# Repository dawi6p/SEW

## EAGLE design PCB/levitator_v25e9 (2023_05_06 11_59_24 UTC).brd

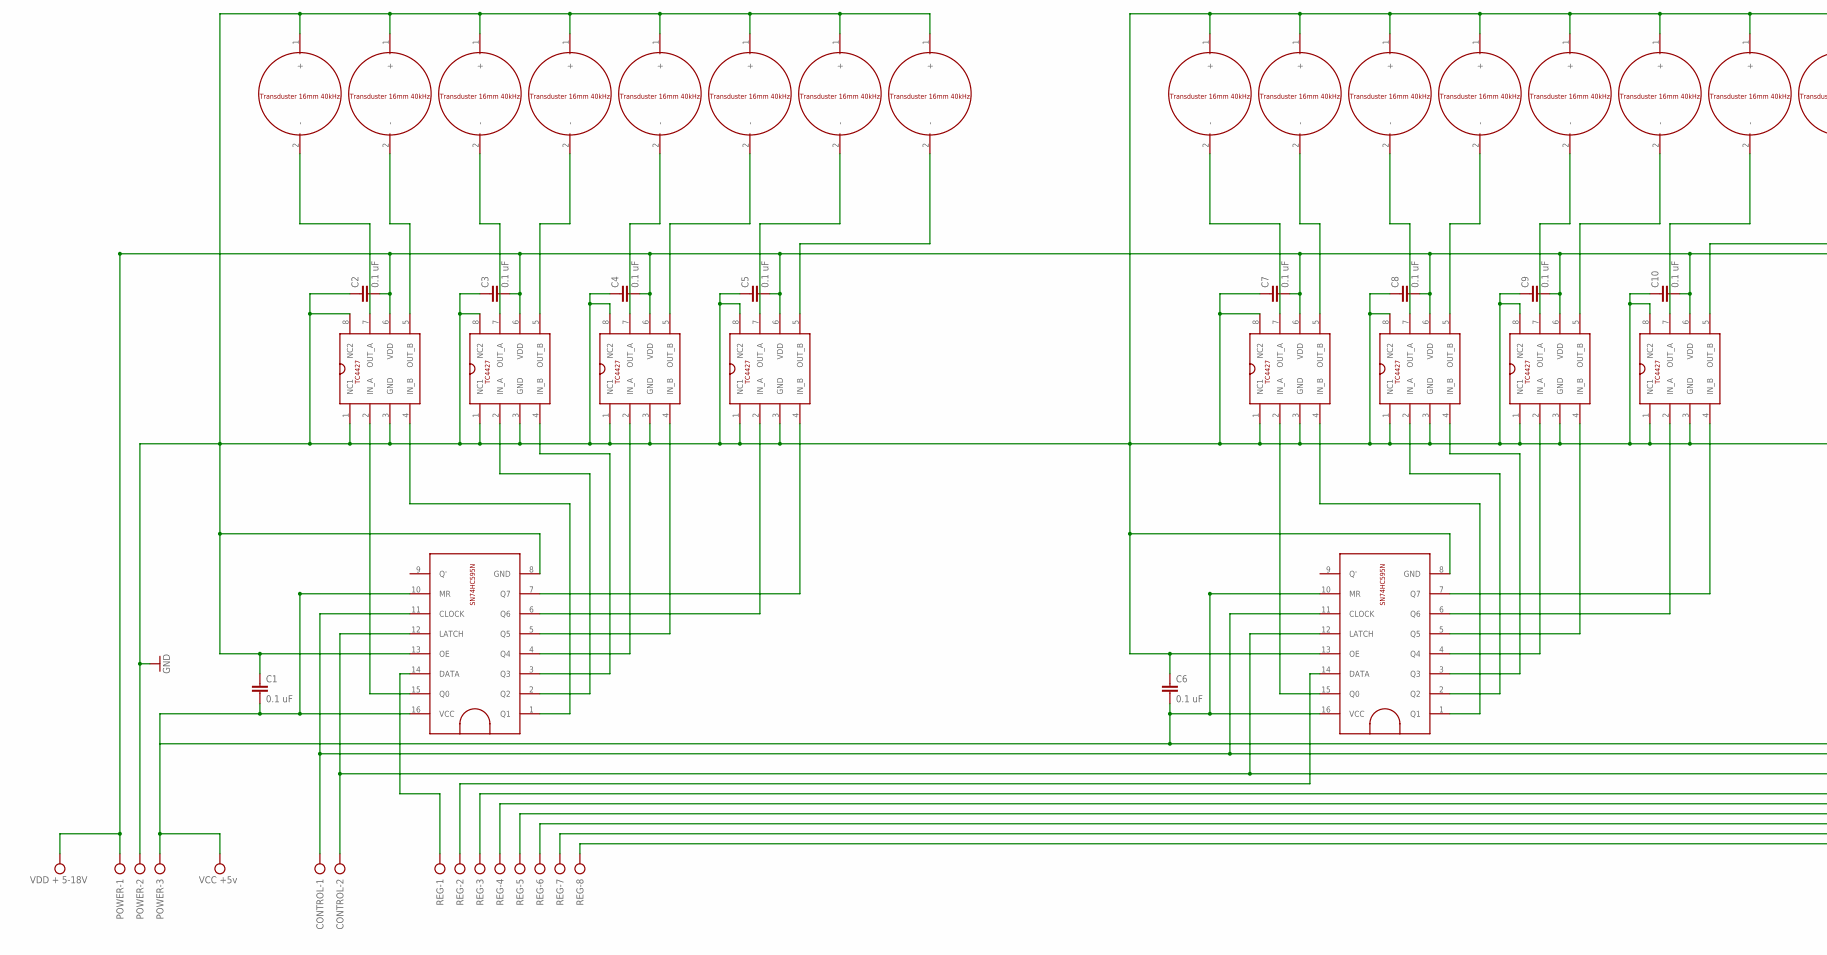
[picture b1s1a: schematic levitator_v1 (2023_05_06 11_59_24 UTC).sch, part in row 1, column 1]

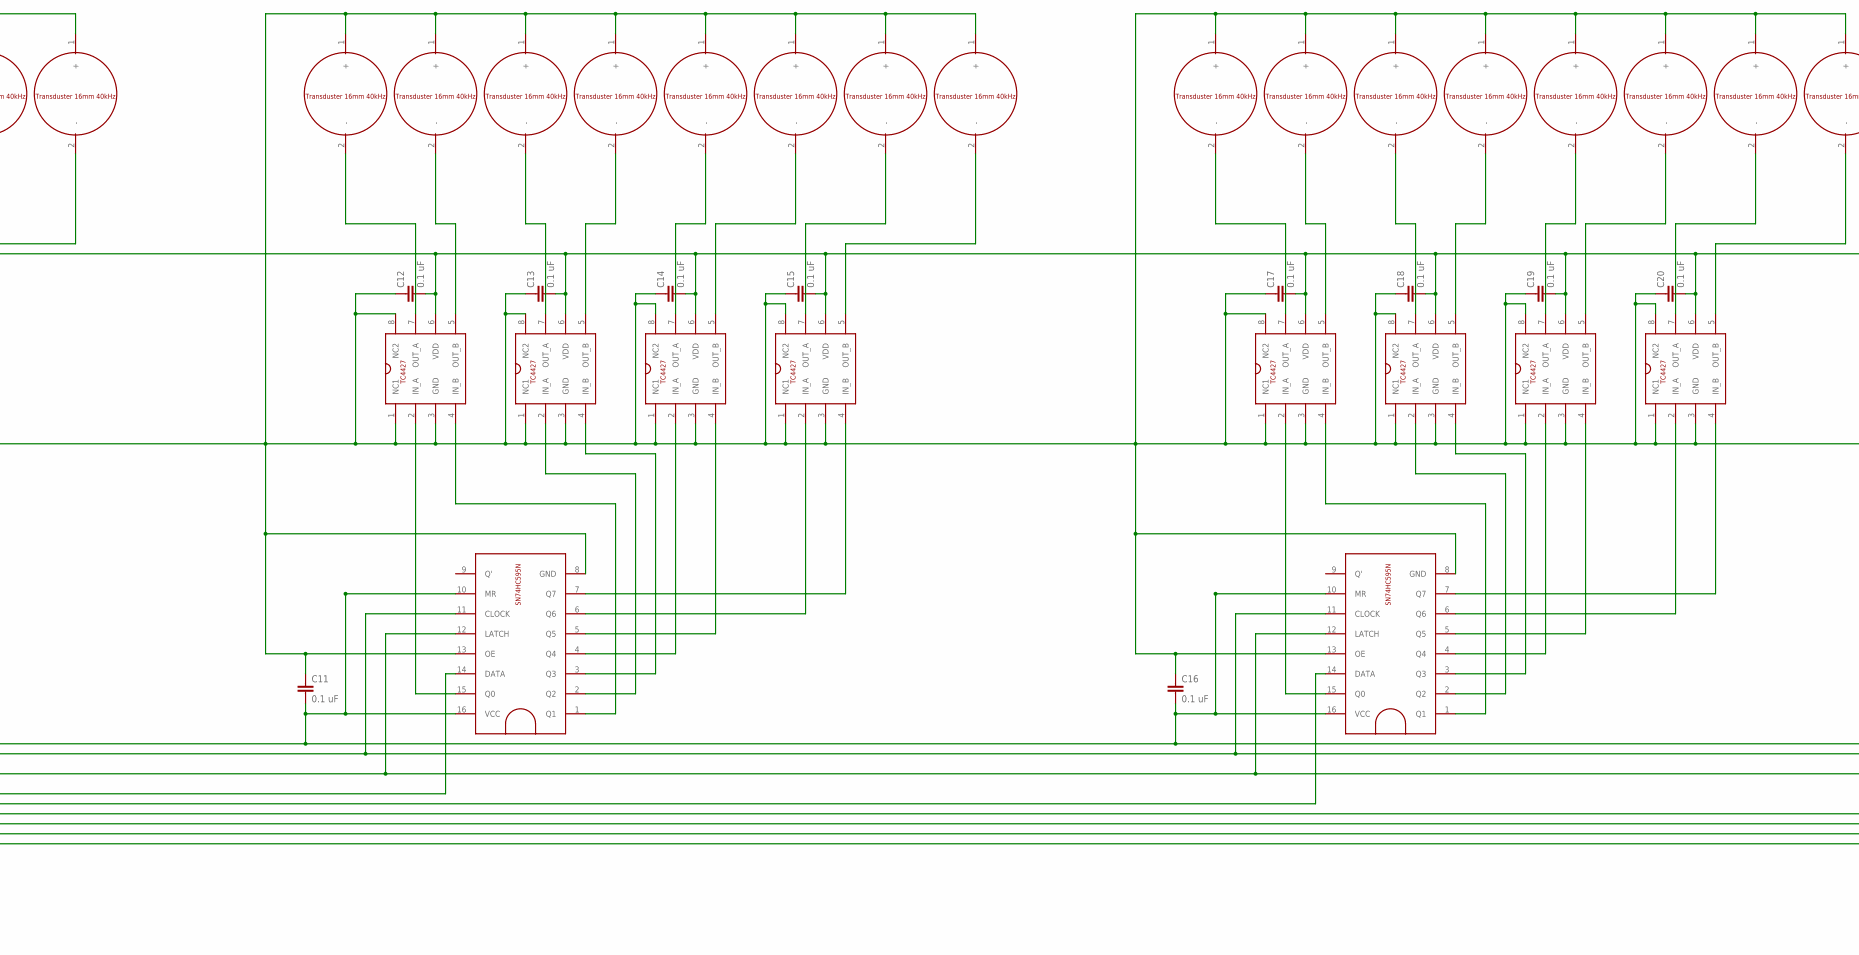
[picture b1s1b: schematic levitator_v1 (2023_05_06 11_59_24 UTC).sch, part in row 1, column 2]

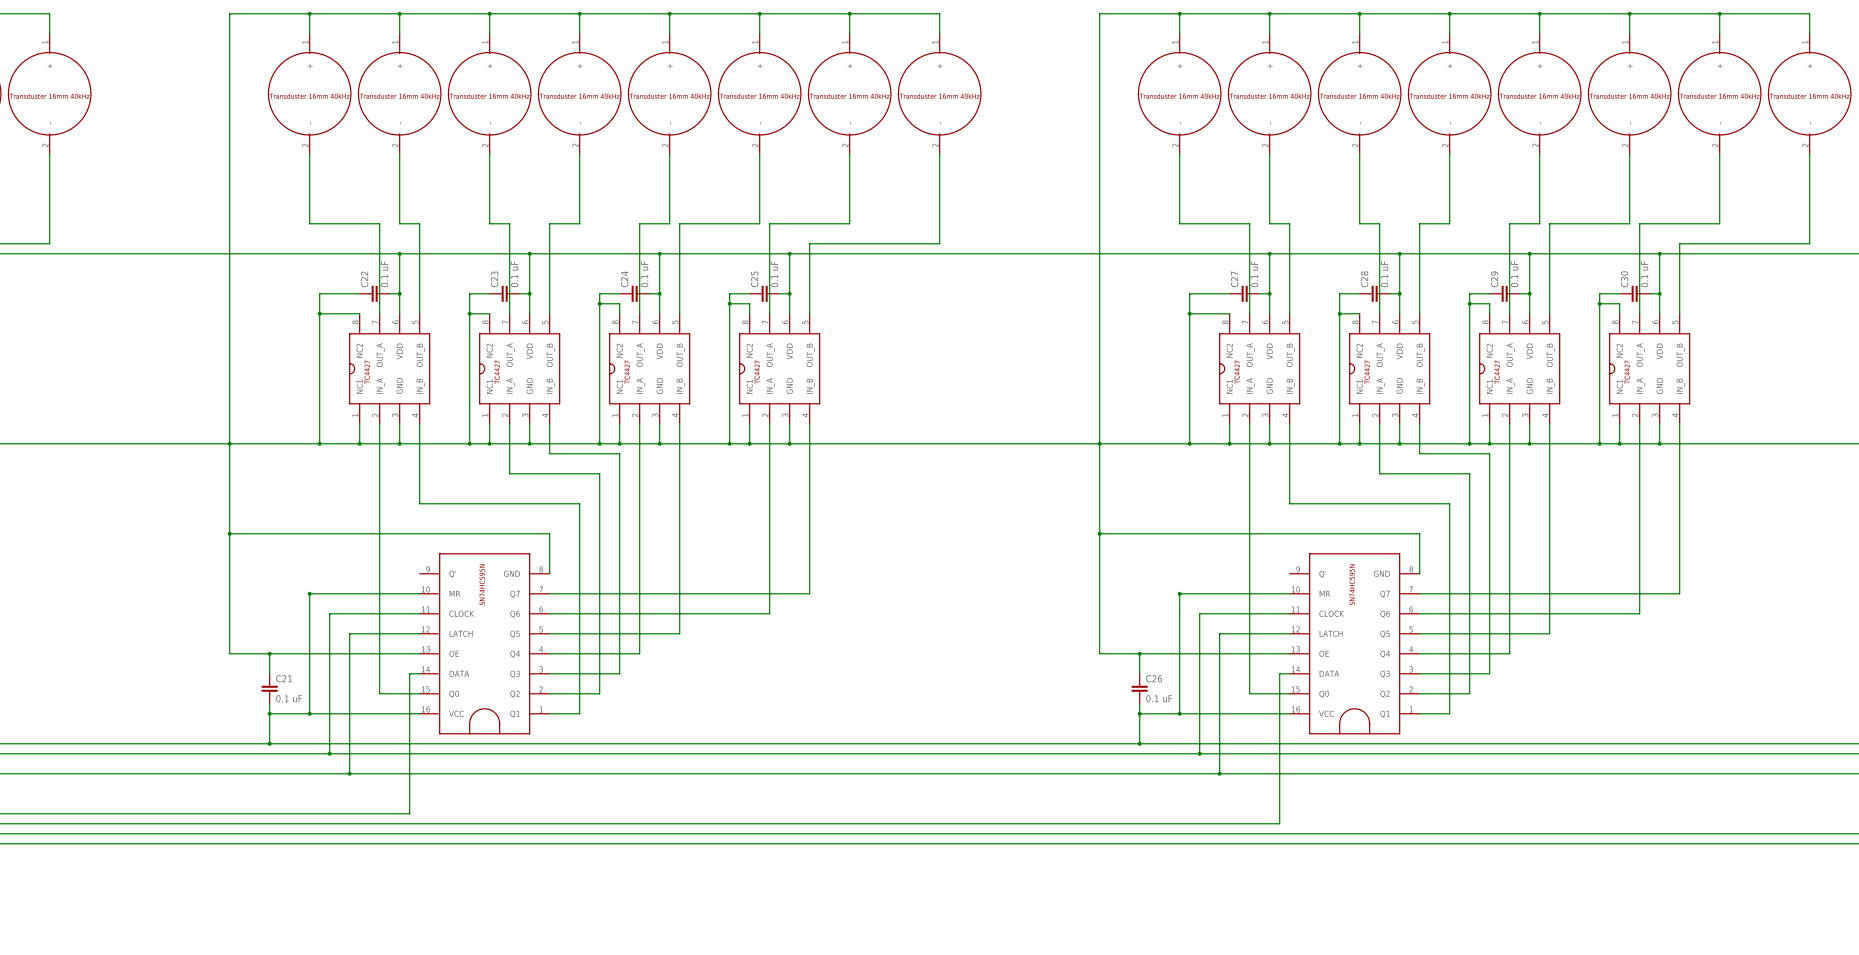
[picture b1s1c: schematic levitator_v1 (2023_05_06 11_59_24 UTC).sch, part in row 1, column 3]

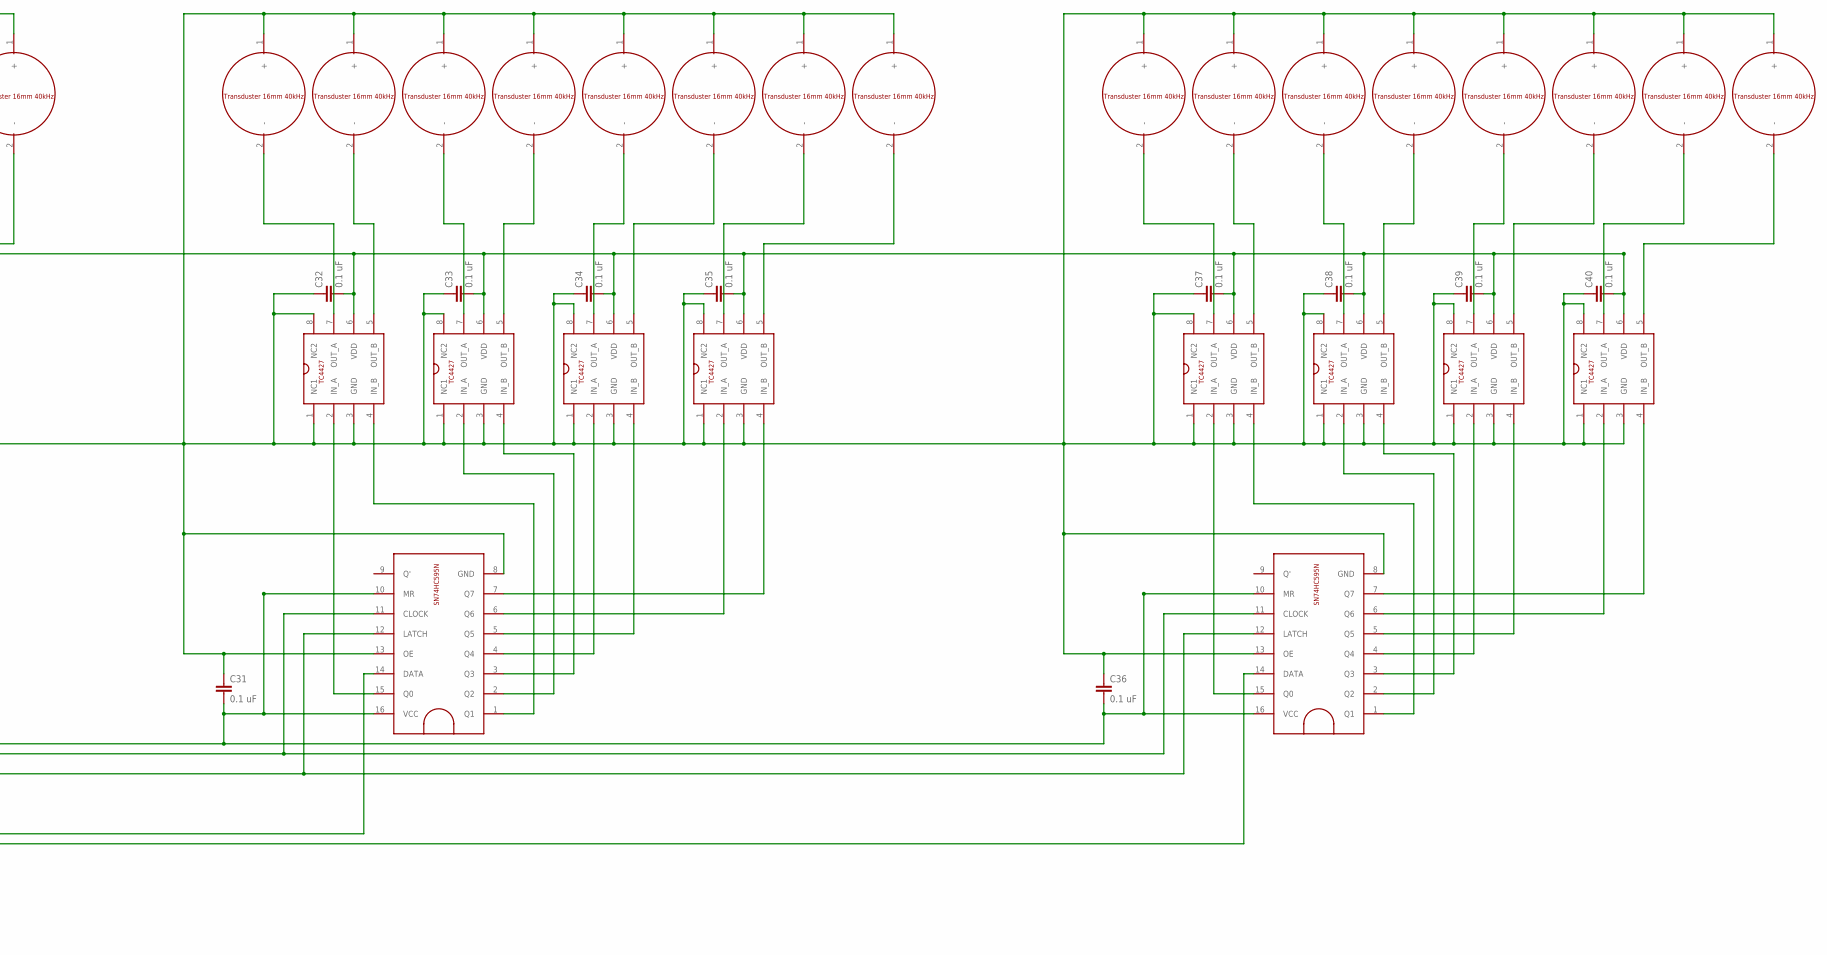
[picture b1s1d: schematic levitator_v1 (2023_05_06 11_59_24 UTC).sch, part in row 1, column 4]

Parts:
C1, C2, C3, C4, C5, C6, C7, C8, C9, C10, C11, C12, C13, C14, C15, C16, C17, C18, C19, C20, C21, C22, C23, C24, C25, C26, C27, C28, C29, C30, C31, C32, C33, C34, C35, C36, C37, C38, C39, C40: 0.1 uF; C025-025X050
CONTROL: AK500/2-H
POWER: AK500/3-H
REG: AK500/8-H
U$1, U$3, U$4, U$5, U$14, U$16, U$17, U$18, U$27, U$29, U$30, U$31, U$40, U$42, U$43, U$44, U$53, U$55, U$56, U$57, U$66, U$68, U$69, U$70, U$79, U$81, U$82, U$83, U$92, U$94, U$95, U$96: TC4427
U$2, U$15, U$28, U$41, U$54, U$67, U$80, U$93: SN74HC595N
U$6, U$7, U$8, U$9, U$10, U$11, U$12, U$13, U$19, U$20, U$21, U$22, U$23, U$24, U$25, U$26, U$32, U$33, U$34, U$35, U$36, U$37, U$38, U$39, U$45, U$46, U$47, U$48, U$49, U$50, U$51, U$52, U$58, U$59, U$60, U$61, U$62, U$63, U$64, U$65, U$71, U$72, U$73, U$74, U$75, U$76, U$77, U$78, U$84, U$85, U$86, U$87, U$88, U$89, U$90, U$91, U$97, U$98, U$99, U$100, U$101, U$102, U$103, U$104: TRANSDUSTER_16MM_40KHZ

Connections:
GND: C1.1, C2.1, C3.1, C4.1, C5.1, C6.1, C7.1, C8.1, C9.1, C10.1, C11.1, C12.1, C13.1, C14.1, C15.1, C16.1, C17.1, C18.1, C19.1, C20.1, C21.1, C22.1, C23.1, C24.1, C25.1, C26.1, C27.1, C28.1, C29.1, C30.1, C31.1, C32.1, C33.1, C34.1, C35.1, C36.1, C37.1, C38.1, C39.1, C40.1, POWER.2, U$1.1 (NC1), U$1.3 (GND), U$1.8 (NC2), U$2.8 (GND), U$2.13 (OE), U$3.1 (NC1), U$3.3 (GND), U$3.8 (NC2), U$4.1 (NC1), U$4.3 (GND), U$4.8 (NC2), U$5.1 (NC1), U$5.3 (GND), U$5.8 (NC2), U$6.1 (+), U$7.1 (+), U$8.1 (+), U$9.1 (+), U$10.1 (+), U$11.1 (+), U$12.1 (+), U$13.1 (+), U$14.1 (NC1), U$14.3 (GND), U$14.8 (NC2), U$15.8 (GND), U$15.13 (OE), U$16.1 (NC1), U$16.3 (GND), U$16.8 (NC2), U$17.1 (NC1), U$17.3 (GND), U$17.8 (NC2), U$18.1 (NC1), U$18.3 (GND), U$18.8 (NC2), U$19.1 (+), U$20.1 (+), U$21.1 (+), U$22.1 (+), U$23.1 (+), U$24.1 (+), U$25.1 (+), U$26.1 (+), U$27.1 (NC1), U$27.3 (GND), U$27.8 (NC2), U$28.8 (GND), U$28.13 (OE), U$29.1 (NC1), U$29.3 (GND), U$29.8 (NC2), U$30.1 (NC1), U$30.3 (GND), U$30.8 (NC2), U$31.1 (NC1), U$31.3 (GND), U$31.8 (NC2), U$32.1 (+), U$33.1 (+), U$34.1 (+), U$35.1 (+), U$36.1 (+), U$37.1 (+), U$38.1 (+), U$39.1 (+), U$40.1 (NC1), U$40.3 (GND), U$40.8 (NC2), U$41.8 (GND), U$41.13 (OE), U$42.1 (NC1), U$42.3 (GND), U$42.8 (NC2), U$43.1 (NC1), U$43.3 (GND), U$43.8 (NC2), U$44.1 (NC1), U$44.3 (GND), U$44.8 (NC2), U$45.1 (+), U$46.1 (+), U$47.1 (+), U$48.1 (+), U$49.1 (+), U$50.1 (+), U$51.1 (+), U$52.1 (+), U$53.1 (NC1), U$53.3 (GND), U$53.8 (NC2), U$54.8 (GND), U$54.13 (OE), U$55.1 (NC1), U$55.3 (GND), U$55.8 (NC2), U$56.1 (NC1), U$56.3 (GND), U$56.8 (NC2), U$57.1 (NC1), U$57.3 (GND), U$57.8 (NC2), U$58.1 (+), U$59.1 (+), U$60.1 (+), U$61.1 (+), U$62.1 (+), U$63.1 (+), U$64.1 (+), U$65.1 (+), U$66.1 (NC1), U$66.3 (GND), U$66.8 (NC2), U$67.8 (GND), U$67.13 (OE), U$68.1 (NC1), U$68.3 (GND), U$68.8 (NC2), U$69.1 (NC1), U$69.3 (GND), U$69.8 (NC2), U$70.1 (NC1), U$70.3 (GND), U$70.8 (NC2), U$71.1 (+), U$72.1 (+), U$73.1 (+), U$74.1 (+), U$75.1 (+), U$76.1 (+), U$77.1 (+), U$78.1 (+), U$79.1 (NC1), U$79.3 (GND), U$79.8 (NC2), U$80.8 (GND), U$80.13 (OE), U$81.1 (NC1), U$81.3 (GND), U$81.8 (NC2), U$82.1 (NC1), U$82.3 (GND), U$82.8 (NC2), U$83.1 (NC1), U$83.3 (GND), U$83.8 (NC2), U$84.1 (+), U$85.1 (+), U$86.1 (+), U$87.1 (+), U$88.1 (+), U$89.1 (+), U$90.1 (+), U$91.1 (+), U$92.1 (NC1), U$92.3 (GND), U$92.8 (NC2), U$93.8 (GND), U$93.13 (OE), U$94.1 (NC1), U$94.3 (GND), U$94.8 (NC2), U$95.1 (NC1), U$95.3 (GND), U$95.8 (NC2), U$96.1 (NC1), U$96.3 (GND), U$96.8 (NC2), U$97.1 (+), U$98.1 (+), U$99.1 (+), U$100.1 (+), U$101.1 (+), U$102.1 (+), U$103.1 (+), U$104.1 (+)
unnamed: U$1.2 (IN_A), U$2.15 (Q0)
unnamed: U$1.4 (IN_B), U$2.1 (Q1)
unnamed: U$2.2 (Q2), U$3.2 (IN_A)
unnamed: U$2.3 (Q3), U$3.4 (IN_B)
unnamed: U$2.4 (Q4), U$4.2 (IN_A)
unnamed: U$2.5 (Q5), U$4.4 (IN_B)
unnamed: U$2.6 (Q6), U$5.2 (IN_A)
unnamed: U$2.7 (Q7), U$5.4 (IN_B)
unnamed: U$1.7 (OUT_A), U$6.2 (-)
unnamed: U$1.5 (OUT_B), U$7.2 (-)
unnamed: U$3.7 (OUT_A), U$8.2 (-)
unnamed: U$3.5 (OUT_B), U$9.2 (-)
unnamed: U$4.7 (OUT_A), U$10.2 (-)
unnamed: U$4.5 (OUT_B), U$11.2 (-)
unnamed: U$5.7 (OUT_A), U$12.2 (-)
unnamed: U$5.5 (OUT_B), U$13.2 (-)
unnamed: REG.1, U$2.14 (DATA)
unnamed: U$79.2 (IN_A), U$80.15 (Q0)
unnamed: U$79.4 (IN_B), U$80.1 (Q1)
unnamed: U$14.2 (IN_A), U$15.15 (Q0)
unnamed: U$14.4 (IN_B), U$15.1 (Q1)
unnamed: U$15.2 (Q2), U$16.2 (IN_A)
unnamed: U$15.3 (Q3), U$16.4 (IN_B)
unnamed: U$15.4 (Q4), U$17.2 (IN_A)
unnamed: U$15.5 (Q5), U$17.4 (IN_B)
unnamed: U$15.6 (Q6), U$18.2 (IN_A)
unnamed: U$15.7 (Q7), U$18.4 (IN_B)
unnamed: U$14.7 (OUT_A), U$19.2 (-)
unnamed: U$14.5 (OUT_B), U$20.2 (-)
unnamed: U$16.7 (OUT_A), U$21.2 (-)
unnamed: U$16.5 (OUT_B), U$22.2 (-)
unnamed: U$17.7 (OUT_A), U$23.2 (-)
unnamed: U$17.5 (OUT_B), U$24.2 (-)
unnamed: U$18.7 (OUT_A), U$25.2 (-)
unnamed: U$18.5 (OUT_B), U$26.2 (-)
unnamed: REG.2, U$15.14 (DATA)
unnamed: U$27.2 (IN_A), U$28.15 (Q0)
unnamed: U$27.4 (IN_B), U$28.1 (Q1)
unnamed: U$28.2 (Q2), U$29.2 (IN_A)
unnamed: U$28.3 (Q3), U$29.4 (IN_B)
unnamed: U$28.4 (Q4), U$30.2 (IN_A)
unnamed: U$28.5 (Q5), U$30.4 (IN_B)
unnamed: U$28.6 (Q6), U$31.2 (IN_A)
unnamed: U$28.7 (Q7), U$31.4 (IN_B)
unnamed: U$27.7 (OUT_A), U$32.2 (-)
unnamed: U$27.5 (OUT_B), U$33.2 (-)
unnamed: U$29.7 (OUT_A), U$34.2 (-)
unnamed: U$29.5 (OUT_B), U$35.2 (-)
unnamed: U$30.7 (OUT_A), U$36.2 (-)
unnamed: U$30.5 (OUT_B), U$37.2 (-)
unnamed: U$31.7 (OUT_A), U$38.2 (-)
unnamed: U$31.5 (OUT_B), U$39.2 (-)
unnamed: REG.3, U$28.14 (DATA)
unnamed: U$80.2 (Q2), U$81.2 (IN_A)
unnamed: CONTROL.1, U$2.11 (CLOCK), U$15.11 (CLOCK), U$28.11 (CLOCK), U$41.11 (CLOCK), U$54.11 (CLOCK), U$67.11 (CLOCK), U$80.11 (CLOCK), U$93.11 (CLOCK)
unnamed: CONTROL.2, U$2.12 (LATCH), U$15.12 (LATCH), U$28.12 (LATCH), U$41.12 (LATCH), U$54.12 (LATCH), U$67.12 (LATCH), U$80.12 (LATCH), U$93.12 (LATCH)
unnamed: U$40.2 (IN_A), U$41.15 (Q0)
unnamed: U$40.4 (IN_B), U$41.1 (Q1)
unnamed: U$41.2 (Q2), U$42.2 (IN_A)
unnamed: U$41.3 (Q3), U$42.4 (IN_B)
unnamed: U$41.4 (Q4), U$43.2 (IN_A)
unnamed: U$41.5 (Q5), U$43.4 (IN_B)
unnamed: U$41.6 (Q6), U$44.2 (IN_A)
unnamed: U$41.7 (Q7), U$44.4 (IN_B)
unnamed: U$40.7 (OUT_A), U$45.2 (-)
unnamed: U$40.5 (OUT_B), U$46.2 (-)
unnamed: U$42.7 (OUT_A), U$47.2 (-)
unnamed: U$42.5 (OUT_B), U$48.2 (-)
unnamed: U$43.7 (OUT_A), U$49.2 (-)
unnamed: U$43.5 (OUT_B), U$50.2 (-)
unnamed: U$44.7 (OUT_A), U$51.2 (-)
unnamed: U$44.5 (OUT_B), U$52.2 (-)
unnamed: REG.4, U$41.14 (DATA)
unnamed: U$80.3 (Q3), U$81.4 (IN_B)
unnamed: U$53.2 (IN_A), U$54.15 (Q0)
unnamed: U$53.4 (IN_B), U$54.1 (Q1)
unnamed: U$54.2 (Q2), U$55.2 (IN_A)
unnamed: U$54.3 (Q3), U$55.4 (IN_B)
unnamed: U$54.4 (Q4), U$56.2 (IN_A)
unnamed: U$54.5 (Q5), U$56.4 (IN_B)
unnamed: U$54.6 (Q6), U$57.2 (IN_A)
unnamed: U$54.7 (Q7), U$57.4 (IN_B)
unnamed: U$53.7 (OUT_A), U$58.2 (-)
unnamed: U$53.5 (OUT_B), U$59.2 (-)
unnamed: U$55.7 (OUT_A), U$60.2 (-)
unnamed: U$55.5 (OUT_B), U$61.2 (-)
unnamed: U$56.7 (OUT_A), U$62.2 (-)
unnamed: U$56.5 (OUT_B), U$63.2 (-)
unnamed: U$57.7 (OUT_A), U$64.2 (-)
unnamed: U$57.5 (OUT_B), U$65.2 (-)
unnamed: REG.5, U$54.14 (DATA)
unnamed: U$66.2 (IN_A), U$67.15 (Q0)
unnamed: U$66.4 (IN_B), U$67.1 (Q1)
unnamed: U$67.2 (Q2), U$68.2 (IN_A)
unnamed: U$67.3 (Q3), U$68.4 (IN_B)
unnamed: U$67.4 (Q4), U$69.2 (IN_A)
unnamed: U$67.5 (Q5), U$69.4 (IN_B)
unnamed: U$67.6 (Q6), U$70.2 (IN_A)
unnamed: U$67.7 (Q7), U$70.4 (IN_B)
unnamed: U$66.7 (OUT_A), U$71.2 (-)
unnamed: U$66.5 (OUT_B), U$72.2 (-)
unnamed: U$68.7 (OUT_A), U$73.2 (-)
unnamed: U$68.5 (OUT_B), U$74.2 (-)
unnamed: U$69.7 (OUT_A), U$75.2 (-)
unnamed: U$69.5 (OUT_B), U$76.2 (-)
unnamed: U$70.7 (OUT_A), U$77.2 (-)
unnamed: U$70.5 (OUT_B), U$78.2 (-)
unnamed: REG.6, U$67.14 (DATA)
unnamed: U$80.4 (Q4), U$82.2 (IN_A)
unnamed: U$80.5 (Q5), U$82.4 (IN_B)
unnamed: U$80.6 (Q6), U$83.2 (IN_A)
unnamed: U$80.7 (Q7), U$83.4 (IN_B)
unnamed: U$79.7 (OUT_A), U$84.2 (-)
unnamed: U$79.5 (OUT_B), U$85.2 (-)
unnamed: U$81.7 (OUT_A), U$86.2 (-)
unnamed: U$81.5 (OUT_B), U$87.2 (-)
unnamed: U$82.7 (OUT_A), U$88.2 (-)
unnamed: U$82.5 (OUT_B), U$89.2 (-)
unnamed: U$83.7 (OUT_A), U$90.2 (-)
unnamed: U$83.5 (OUT_B), U$91.2 (-)
unnamed: REG.7, U$80.14 (DATA)
unnamed: U$92.2 (IN_A), U$93.15 (Q0)
unnamed: U$92.4 (IN_B), U$93.1 (Q1)
unnamed: U$93.2 (Q2), U$94.2 (IN_A)
unnamed: U$93.3 (Q3), U$94.4 (IN_B)
unnamed: U$93.4 (Q4), U$95.2 (IN_A)
unnamed: U$93.5 (Q5), U$95.4 (IN_B)
unnamed: U$93.6 (Q6), U$96.2 (IN_A)
unnamed: U$93.7 (Q7), U$96.4 (IN_B)
unnamed: U$92.7 (OUT_A), U$97.2 (-)
unnamed: U$92.5 (OUT_B), U$98.2 (-)
unnamed: U$94.7 (OUT_A), U$99.2 (-)
unnamed: U$94.5 (OUT_B), U$100.2 (-)
unnamed: U$95.7 (OUT_A), U$101.2 (-)
unnamed: U$95.5 (OUT_B), U$102.2 (-)
unnamed: U$96.7 (OUT_A), U$103.2 (-)
unnamed: U$96.5 (OUT_B), U$104.2 (-)
unnamed: REG.8, U$93.14 (DATA)
VCC: C1.2, C6.2, C11.2, C16.2, C21.2, C26.2, C31.2, C36.2, POWER.3, U$2.10 (MR), U$2.16 (VCC), U$15.10 (MR), U$15.16 (VCC), U$28.10 (MR), U$28.16 (VCC), U$41.10 (MR), U$41.16 (VCC), U$54.10 (MR), U$54.16 (VCC), U$67.10 (MR), U$67.16 (VCC), U$80.10 (MR), U$80.16 (VCC), U$93.10 (MR), U$93.16 (VCC)
VDD: C2.2, C3.2, C4.2, C5.2, C7.2, C8.2, C9.2, C10.2, C12.2, C13.2, C14.2, C15.2, C17.2, C18.2, C19.2, C20.2, C22.2, C23.2, C24.2, C25.2, C27.2, C28.2, C29.2, C30.2, C32.2, C33.2, C34.2, C35.2, C37.2, C38.2, C39.2, C40.2, POWER.1, U$1.6 (VDD), U$3.6 (VDD), U$4.6 (VDD), U$5.6 (VDD), U$14.6 (VDD), U$16.6 (VDD), U$17.6 (VDD), U$18.6 (VDD), U$27.6 (VDD), U$29.6 (VDD), U$30.6 (VDD), U$31.6 (VDD), U$40.6 (VDD), U$42.6 (VDD), U$43.6 (VDD), U$44.6 (VDD), U$53.6 (VDD), U$55.6 (VDD), U$56.6 (VDD), U$57.6 (VDD), U$66.6 (VDD), U$68.6 (VDD), U$69.6 (VDD), U$70.6 (VDD), U$79.6 (VDD), U$81.6 (VDD), U$82.6 (VDD), U$83.6 (VDD), U$92.6 (VDD), U$94.6 (VDD), U$95.6 (VDD), U$96.6 (VDD)

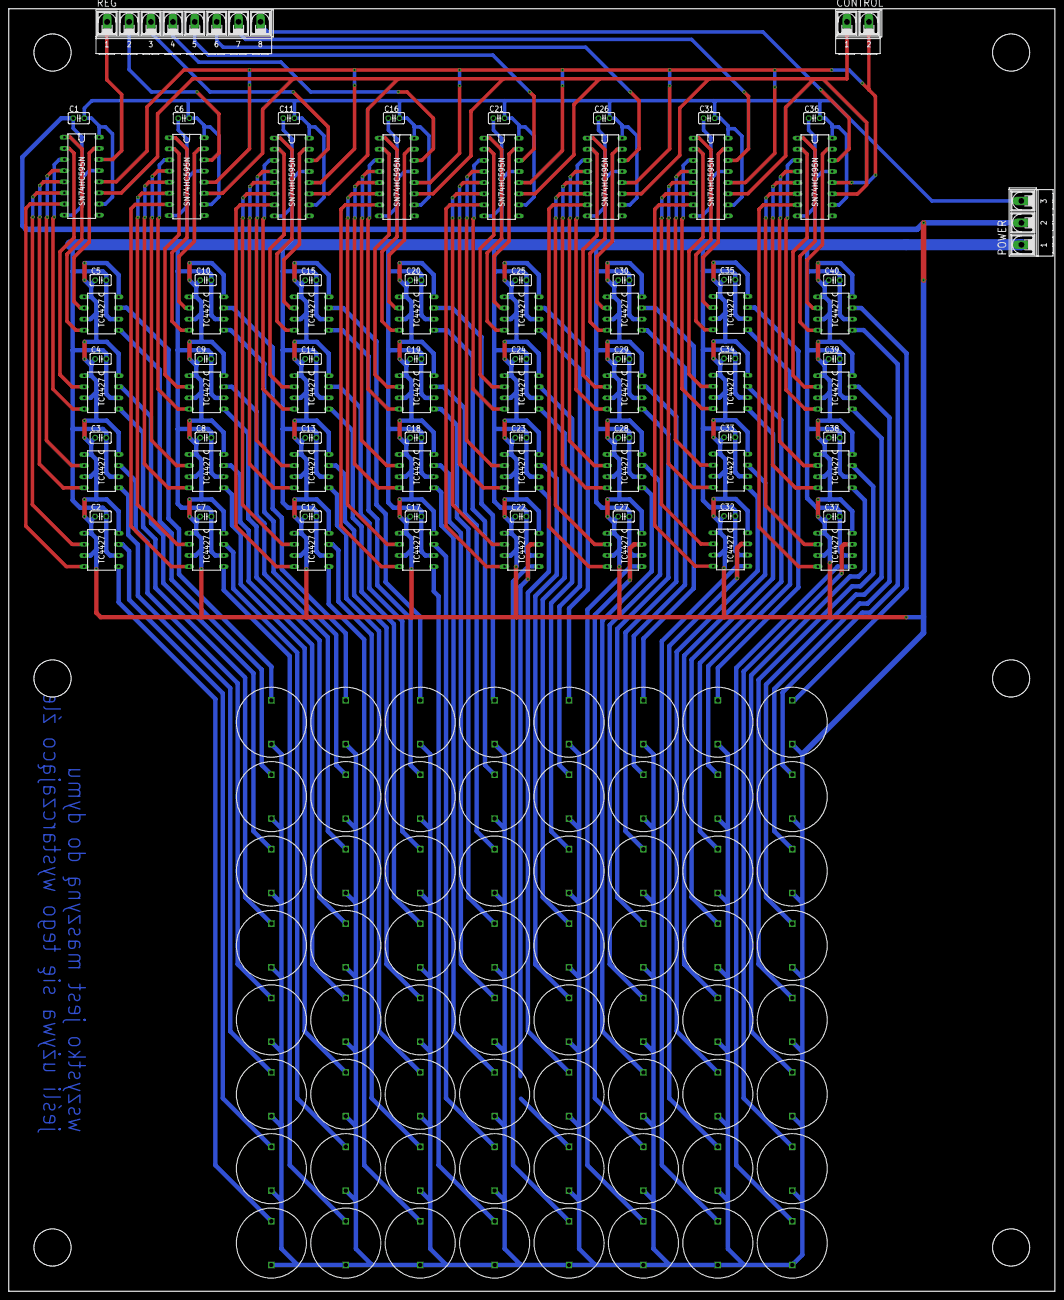
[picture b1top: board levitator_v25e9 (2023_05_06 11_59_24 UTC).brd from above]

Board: 2 copper layers, 239.0 x 293.0 mm, 147 parts (0 on the bottom side), 141 nets.

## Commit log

2023-11-07 pcb schematics
2023-11-12 added stuff
2023-11-13 normalizacja fazy
2023-11-14 small changes
2023-11-15 using math definitons
2023-11-15 made everything into a class
2023-11-16 added mapping of phase onto inteager
2023-11-16 basic ui
2023-11-17 changed shit
2023-11-18 calculating distance with speker diamater
2023-11-19 added funtcion calculating botle trap
2023-11-19 small corection
2023-11-20 no comment
2023-11-21 added functionality to change traps
2023-11-22 optymized trap calculations
2023-11-23 dadded comented data transfer
2023-11-24 nothing
2023-11-26 improved sig shift
2023-11-27 costam
2023-12-04 rzeczy zrobione
2023-12-09 kto zrobil ten blod ostrzerzeniem a nie bledem
2023-12-10 added correction values
